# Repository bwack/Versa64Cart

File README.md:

/pictures/logo.png)

Versa64Cart is designed to be a modern easy-to-use cartridge development board for Commodore 64 and Commodore 128 hobbyists and hackers. The versatile design of the PCB allows for flexible implementation of various cartridge types. Whether it’s a simple cartridge backup of an 8k game or a switchable multi-program diagnostic cartridge, Versa64Cart has you covered.

Supported EPROMS are: 27C64 (8k), 27C128 (16k), 27C256 (32k), 27C512 (64k).
Please see the documentation for more information.

I have put the rev 1.1 in a separate folder in case someone wants to use the kicad files as a template.
Rev. 1.2 and onwards is designed by [Sven Petersen](https://github.com/svenpetersen1965 "Sven's github repository!") in eagle. It is a complete redrawn schematic and layout.

Sven has designed another cartridge called [Diag64cart](https://github.com/svenpetersen1965/Diag64cart) derived from this project.

# Quick Guide

## Obtaining binaries

Use the cartconv.exe tool from the VICE emulator to get information and to extract the binary from .CRT files. Copy it to the same folder as your .CRT files.

List the .CRT information:

```
C:\cartconv>cartconv -f deadtest.CRT
CRT Version: 1.0
Name: C64DEADTESTREV718220
Hardware ID: 0 (Generic Cartridge)
Mode: exrom: 1 game: 0 (ultimax)

offset  sig  type  bank start size  chunklen
$000040 CHIP ROM   #000 $e000 $2000 $2010

total banks: 1 size: $002000
```
The hardware ID must be 0. The size of the eprom shown here is 8k ($2000).

Convert the binary:

`cartconv -i mycartridge.crt -o mycartridge.bin`

## Combining binaries

The Versa64Cart supports EPROMS from 8k to 8x8k or 4x16k. The easiest way to combine is to use the copy command (in Windows):

`copy /b DeadTest.bin + jupiterl.bin + SomeGame.bin combined.bin`

Special care must be taken if mix 8k and 16k images. The 8k binaries must be allocated in pairs:

`copy /b first8k.bin + second8k.bin + some16k.bin combined.bin`

## Documentation

For more information Please see the [pdf file](v1.6/pdf/Versa64cart_v1_6.pdf) in this repository.

## Pictures

# Changes
## 1.6
- Change: Notches added to fit the thefuturewas8bit.com stumpy cartridge case (not the button hole!)

## 1.5
- Change: Combined footprint SW1, 5Way-DIP and 2x5 2.54mm pin header

## 1.4
- Change: card edge connector with pads like in v1.1

## 1.3
- Change: Cartridge enclosure support
  - Moved IC socket away from edge
  - Moved diode group away from edge
  - Bom: Use right angle pin headers. The straight ones are too tall.
  
## 1.2
- A reset button
- Jumpers accessible on outer edge.*
- Solder jumpers at the top layer
- New documentation
- Designed in Eagle
* Remember to turn off the computer before changing the jumpers.

/pictures/Versa64Cart_scan_both_sides.jpg)

## 1.1 and 1.0

- Designed in KiCad based on simple64cart eagle files
- Support retro innovation cartridge enclosure (allthough pins too high)
- Moved IC sockets further from edge
- Added 16k game support
- Added dip switch and jumpers
- Added Documentation

# External websites

[Blog post, "Versa64Cart and C64 ROMs", by Gregory Nacu at c64os.com ](https://c64os.com/post/versa64cart)

# Versa64Cart on YouTube

https://www.youtube.com/results?search_query=Versa64Cart

# VersaZIF64
Check out VersaZIF64 if you are interested in the Versa64cart and with a ZIF socket.
https://github.com/bwack/VersaZIF64

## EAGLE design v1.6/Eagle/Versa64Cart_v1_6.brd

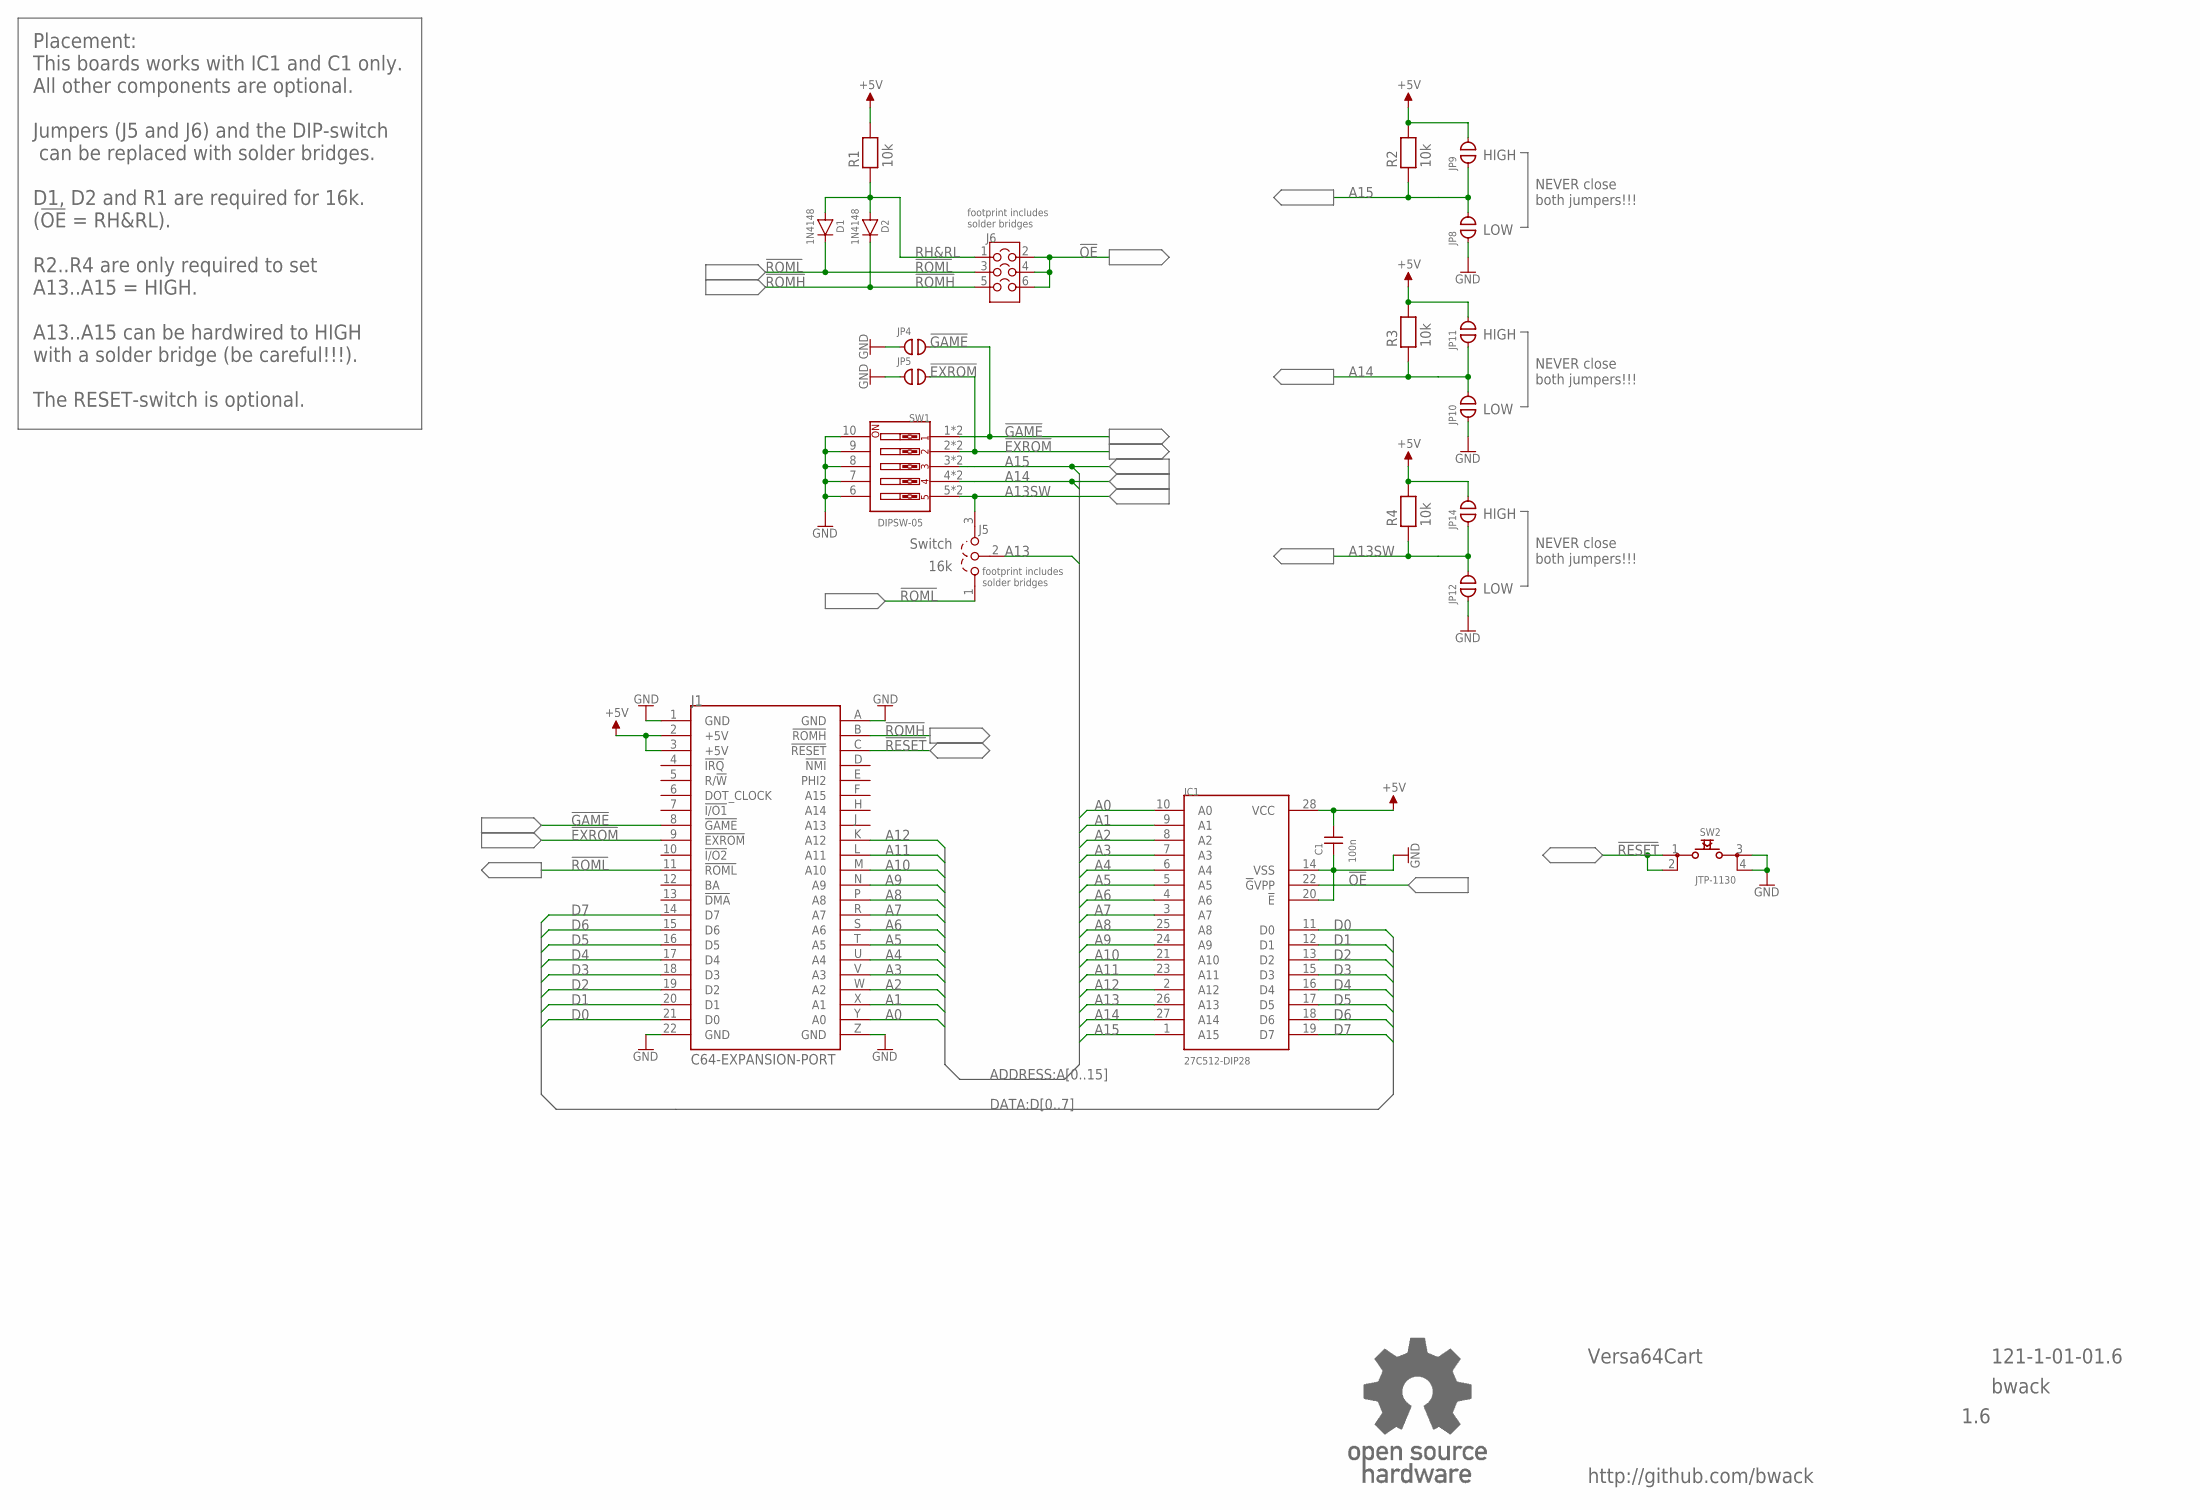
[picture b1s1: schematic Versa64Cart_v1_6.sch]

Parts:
C1: 100n; C-2,5
D1, D2: 1N4148; DO-35
IC1: 27C512-DIP28; DIL28-6
J1: C64-EXPANSION-PORT; EXPANSIO_SQ
J5: COMBI-3P
J6: COMBI-3X2P; COMBI-3X2
JP4, JP5, JP8, JP9, JP10, JP11, JP12, JP14: OPEN; CP_OP
R1, R2, R3, R4: 10k; R-10
SW1: DIPSW-05; DIPSW-05VJ
SW2: JTP-1130
U$43: OPEN_SOURCE_HW; OPENHW

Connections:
!EXROM: J1.9 (!EXROM), JP5.2, SW1.2, SW1.2J (2)
!GAME: J1.8 (!GAME), JP4.2, SW1.1, SW1.1J (1)
!OE: IC1.22 (!G!VPP), J6.2, J6.4, J6.6
!RESET: J1.C (!RESET), SW2.1, SW2.2
!ROMH: D2.K, J1.B (!ROMH), J6.5
!ROML: D1.K, J1.11 (!ROML), J5.1, J6.3
+5V: C1.2, IC1.28 (VCC), J1.2 (+5V), J1.3 (+5V), JP9.2, JP11.2, JP14.2, R1.2, R2.2, R3.2, R4.2
A0: IC1.10 (A0), J1.Y (A0)
A1: IC1.9 (A1), J1.X (A1)
A2: IC1.8 (A2), J1.W (A2)
A3: IC1.7 (A3), J1.V (A3)
A4: IC1.6 (A4), J1.U (A4)
A5: IC1.5 (A5), J1.T (A5)
A6: IC1.4 (A6), J1.S (A6)
A7: IC1.3 (A7), J1.R (A7)
A8: IC1.25 (A8), J1.P (A8)
A9: IC1.24 (A9), J1.N (A9)
A10: IC1.21 (A10), J1.M (A10)
A11: IC1.23 (A11), J1.L (A11)
A12: IC1.2 (A12), J1.K (A12)
A13: IC1.26 (A13), J5.2
A13SW: J5.3, JP12.2, JP14.1, R4.1, SW1.5, SW1.5J (5)
A14: IC1.27 (A14), JP10.2, JP11.1, R3.1, SW1.4, SW1.4J (4)
A15: IC1.1 (A15), JP8.2, JP9.1, R2.1, SW1.3, SW1.3J (3)
D0: IC1.11 (D0), J1.21 (D0)
D1: IC1.12 (D1), J1.20 (D1)
D2: IC1.13 (D2), J1.19 (D2)
D3: IC1.15 (D3), J1.18 (D3)
D4: IC1.16 (D4), J1.17 (D4)
D5: IC1.17 (D5), J1.16 (D5)
D6: IC1.18 (D6), J1.15 (D6)
D7: IC1.19 (D7), J1.14 (D7)
GND: C1.1, IC1.14 (VSS), IC1.20 (!E), J1.1 (GND), J1.22 (GND), J1.A (GND), J1.Z (GND), JP4.1, JP5.1, JP8.1, JP10.1, JP12.1, SW1.6, SW1.7, SW1.8, SW1.9, SW1.10, SW2.3, SW2.4
RH&RL: D1.A, D2.A, J6.1, R1.1

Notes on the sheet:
LOW
HIGH
NEVER close both jumpers!!!
Versa64Cart
bwack
1.6
footprint includes solder bridges
121-1-01-01.6
Placement: This boards works with IC1 and C1 only. All other components are optional. Jumpers (J5 and J6) and the DIP-switch can be replaced with solder bridges. D1, D2 and R1 are required for 16k. (!OE! = RH&RL). R2..R4 are only required to set A13..A15 = HIGH. A13..A15 can be hardwired to HIGH wi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
16k
Switch
http://github.com/bwack

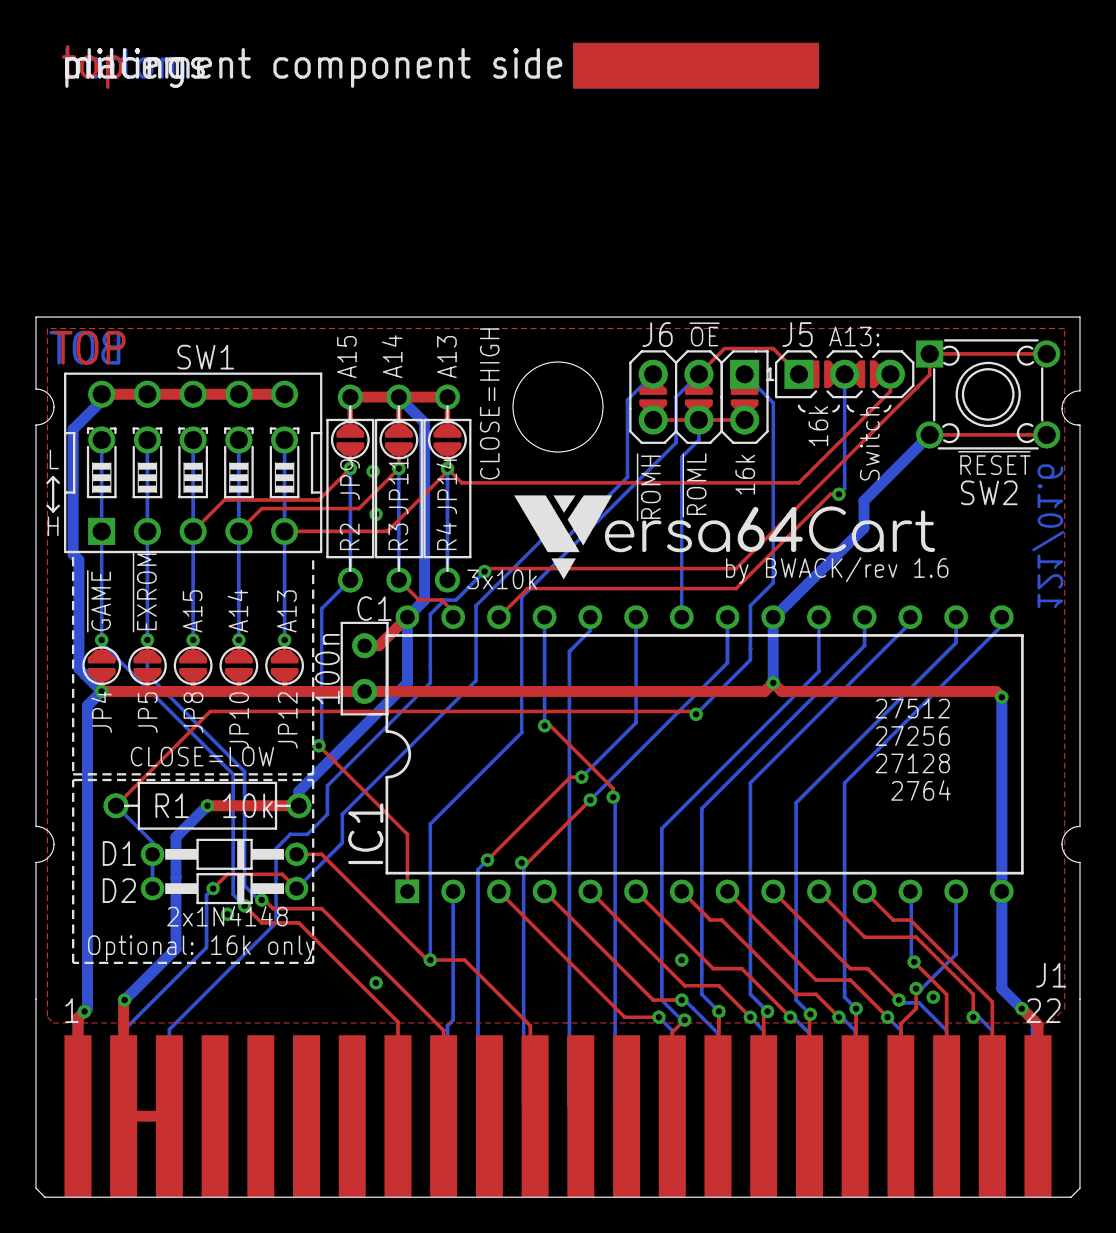
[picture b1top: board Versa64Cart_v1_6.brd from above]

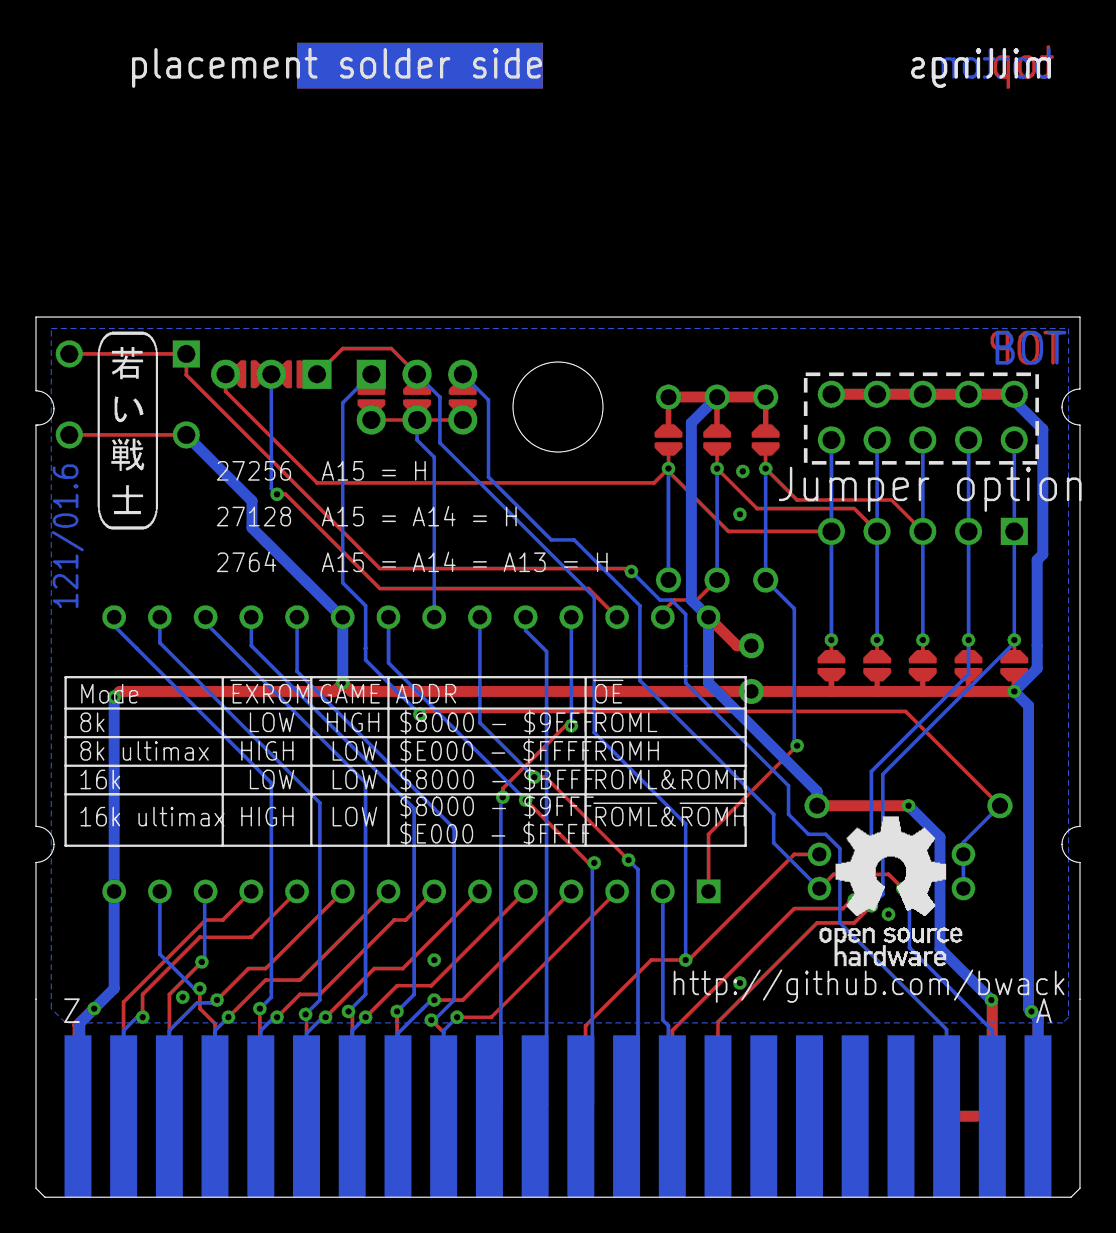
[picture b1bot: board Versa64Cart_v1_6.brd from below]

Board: 2 copper layers, 58.0 x 48.9 mm, 26 parts (2 on the bottom side), 34 nets.

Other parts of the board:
U$39: VERSA64CART
U$40: 2LAYER
U$41: PCB-TITLE/
U$42: SVEN_TAG

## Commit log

2017-06-27 :tada: Added .gitattributes & .gitignore files
2017-06-27 first commit 1.0
2017-06-27 3D render
2017-06-27 the pcb image file
2017-06-27 changed NPTH pad to be NP
2017-06-27 NPTH NP
2017-06-29 VersaCart logo
2017-07-22 Rev 1.1 - missing trace on ROML
2017-09-08 User Guide, not finished
2017-09-08 User Guide
2017-09-08 User guide V0.11
2017-09-08 User Guide V0.12
2017-09-08 User Guide V0.13
2017-09-08 User Guide V0.14
2017-09-09 User Guide V.15 DIP switches
2017-09-11 User Guide V0.16
2017-09-27 gerbers
    tested with dirtypcbs. No extended attributes to support chinese fabs
    with CAM350 software.
2017-09-27 User Guide V0.17 minor changes
2018-01-08 vet ikke hvorfor denne endret seg
2018-01-08 100nF
2018-04-17 online bom #1
2018-05-06 User Guide V0.18: Board dimentions and enclosures.
2018-09-22 Change: Documentation, dead test example. Using large eprom with single 8k image.
2018-09-22 Change: Docs/dead test cart example. Using eprom larger than 27C64 #4
2018-09-22 Change: Docs/Other notes: does kernal roms on the cartridge work #3
2019-04-18 Removed Gerbers catalogue with incorrect gerber file #5
    There is a gerbers.zip file though
2019-05-25 Include v1.2 from Sven
2019-05-25 Released Rev. 1.2
    Rev. 1.2 adds some cosmetic changes to Rev 1.1. The jumpers have been moved to the outer edge of the board and a reset switch has been added.
2019-05-26 readme in v1.1
2019-05-30 new v1.3 files and readme
2019-05-30 changed to right angle pinheaders
2019-05-30 right angle pinheaders in docs and bom
2019-05-30 comma separate file
    github didn't like the colon separated file.
2019-05-30 no idea
2019-06-25 Rev 1.4
2019-11-23 Updated readme with info on combining binaries #11
2019-11-27 Add files via upload
    Enhanced the documentation. Chapter about merging more than one *.bin to an image.bin for the eprom. Module description v1.4a
2019-11-27 Add files via upload
    Added the pictures for the extended documentation.
2020-05-07 combined footprint SW1, 5way DIP switch and 2x5 way 2.54mm pin header
2020-10-18 Updated documentation (pdf). Fixed mistake in table on page 7. #16
2021-12-20 v1.6: added notches for the stumpy cart
2021-12-20 readme update
